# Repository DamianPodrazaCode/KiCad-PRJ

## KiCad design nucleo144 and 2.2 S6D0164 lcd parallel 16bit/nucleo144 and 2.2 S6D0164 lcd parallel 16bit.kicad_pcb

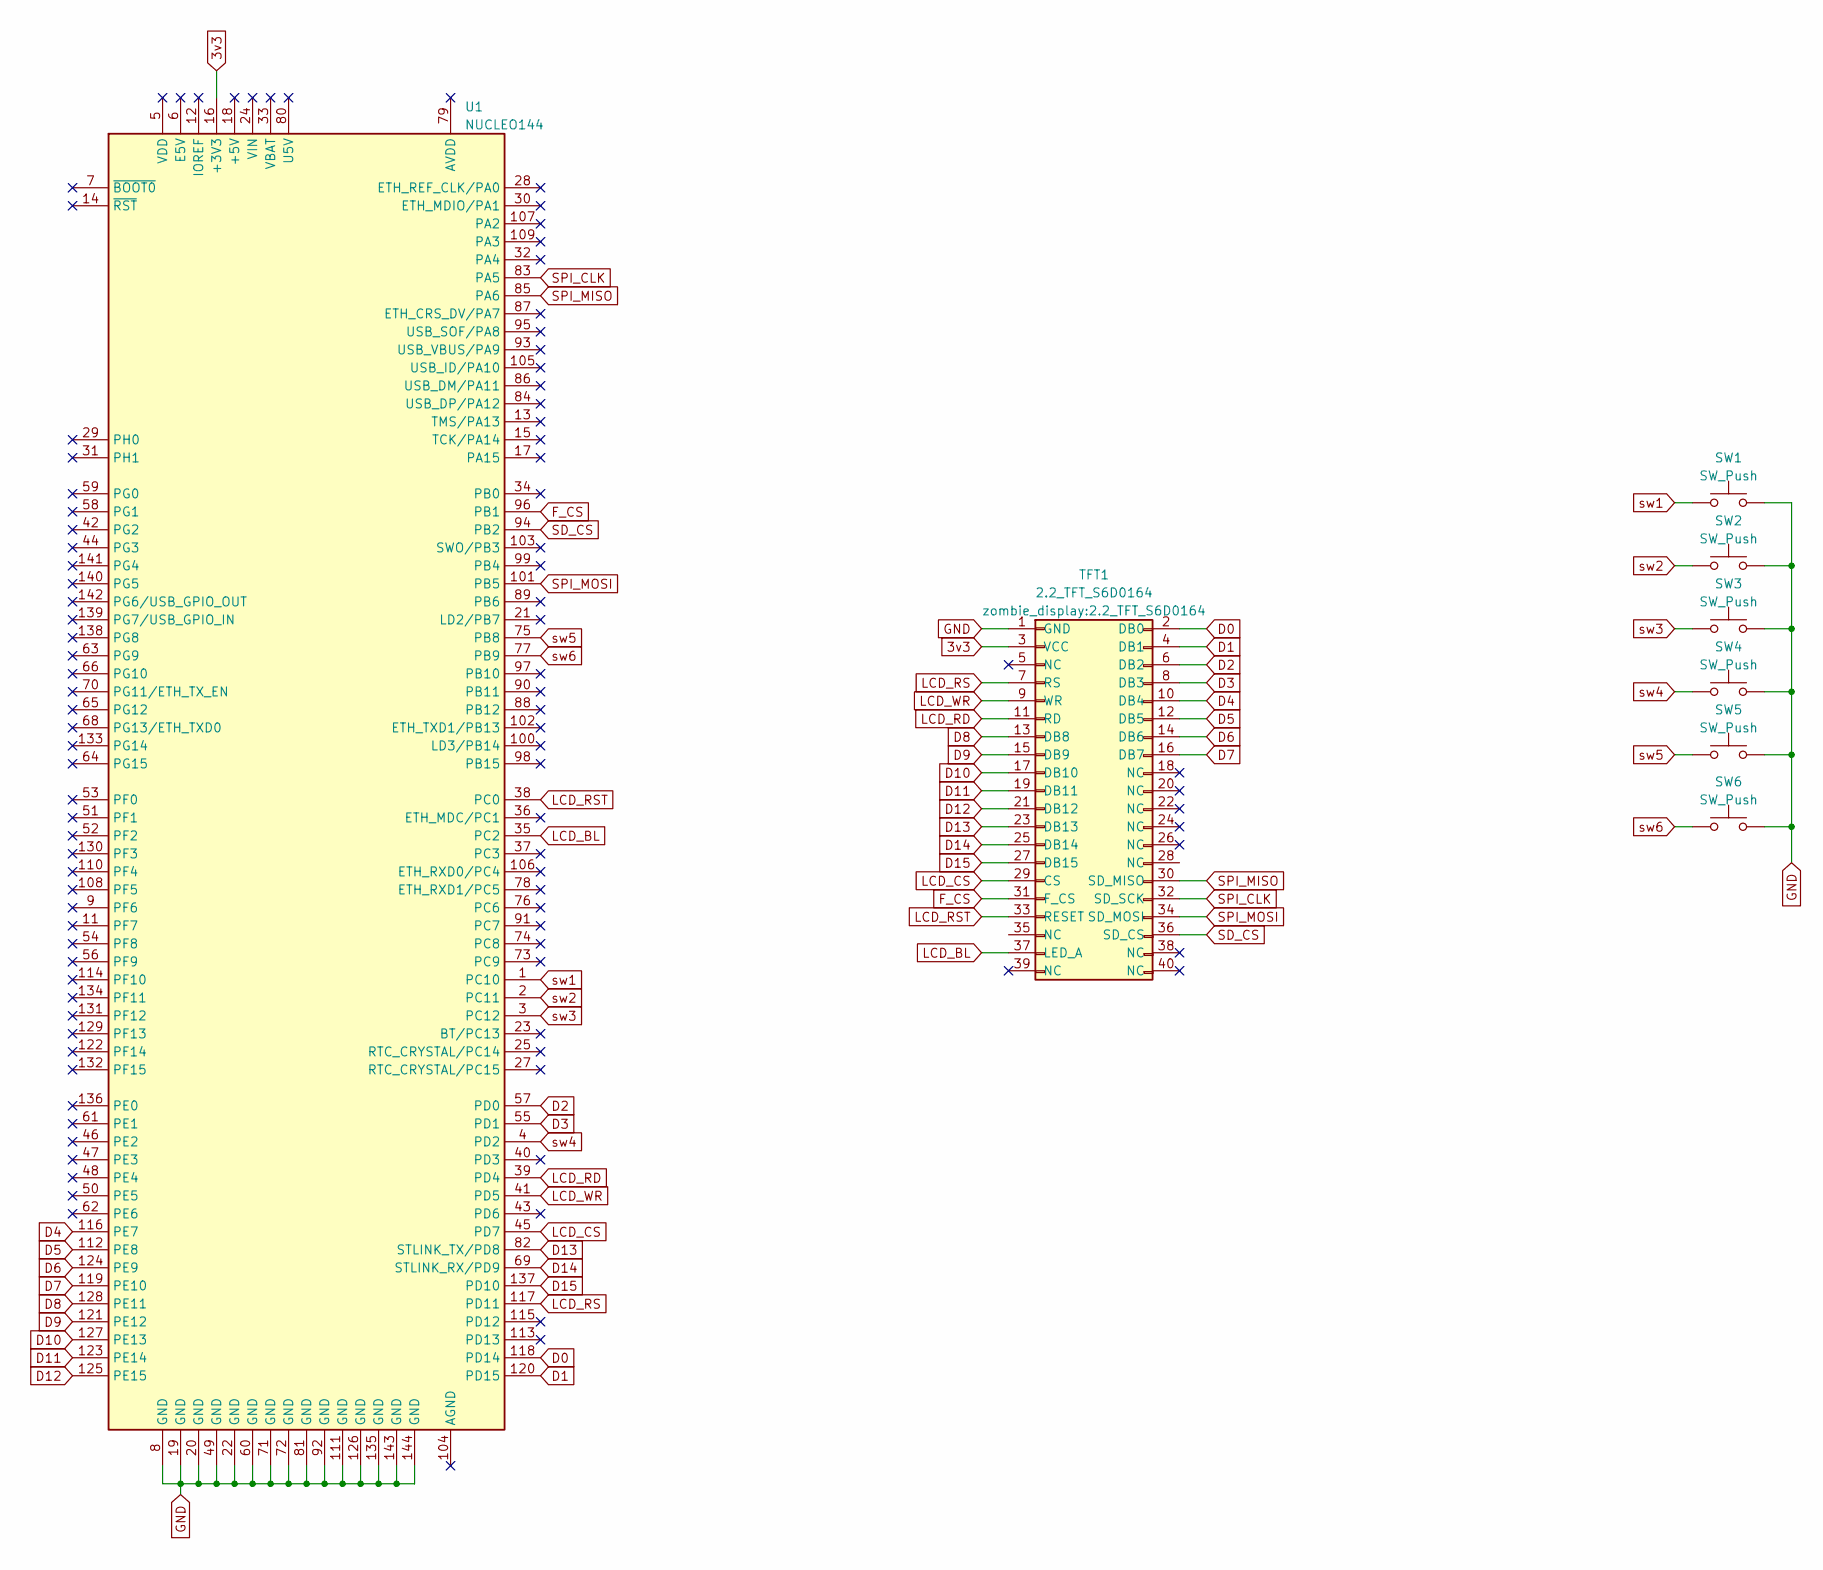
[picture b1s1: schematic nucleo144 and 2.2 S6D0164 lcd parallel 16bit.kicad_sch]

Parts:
SW1, SW2, SW3, SW4, SW5, SW6: SW_Push; SW_PUSH_6mm
TFT1: 2.2_TFT_S6D0164
U1: NUCLEO144; ST_Morpho_Connector_144_Short

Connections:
3v3: TFT1.3 (VCC), U1.16 (+3V3)
D0: TFT1.2 (DB0), U1.118 (PD14)
D1: TFT1.4 (DB1), U1.120 (PD15)
D2: TFT1.6 (DB2), U1.57 (PD0)
D3: TFT1.8 (DB3), U1.55 (PD1)
D4: TFT1.10 (DB4), U1.116 (PE7)
D5: TFT1.12 (DB5), U1.112 (PE8)
D6: TFT1.14 (DB6), U1.124 (PE9)
D7: TFT1.16 (DB7), U1.119 (PE10)
D8: TFT1.13 (DB8), U1.128 (PE11)
D9: TFT1.15 (DB9), U1.121 (PE12)
D10: TFT1.17 (DB10), U1.127 (PE13)
D11: TFT1.19 (DB11), U1.123 (PE14)
D12: TFT1.21 (DB12), U1.125 (PE15)
D13: TFT1.23 (DB13), U1.82 (STLINK_TX/PD8)
D14: TFT1.25 (DB14), U1.69 (STLINK_RX/PD9)
D15: TFT1.27 (DB15), U1.137 (PD10)
F_CS: TFT1.31 (F_CS), U1.96 (PB1)
GND: SW1.2, SW2.2, SW3.2, SW4.2, SW5.2, SW6.2, TFT1.1 (GND), U1.8 (GND), U1.19 (GND), U1.20 (GND), U1.22 (GND), U1.49 (GND), U1.60 (GND), U1.71 (GND), U1.72 (GND), U1.81 (GND), U1.92 (GND), U1.111 (GND), U1.126 (GND), U1.135 (GND), U1.143 (GND), U1.144 (GND)
LCD_BL: TFT1.37 (LED_A), U1.35 (PC2)
LCD_CS: TFT1.29 (CS), U1.45 (PD7)
LCD_RD: TFT1.11 (RD), U1.39 (PD4)
LCD_RS: TFT1.7 (RS), U1.117 (PD11)
LCD_RST: TFT1.33 (RESET), U1.38 (PC0)
LCD_WR: TFT1.9 (WR), U1.41 (PD5)
PEN: U1.37 (PC3)
SD_CS: TFT1.36 (SD_CS), U1.94 (PB2)
SPI_CLK: TFT1.32 (SD_SCK), U1.83 (PA5)
SPI_MISO: TFT1.30 (SD_MISO), U1.85 (PA6)
SPI_MOSI: TFT1.34 (SD_MOSI), U1.101 (PB5)
T_CS: U1.109 (PA3)
sw1: SW1.1, U1.1 (PC10)
sw2: SW2.1, U1.2 (PC11)
sw3: SW3.1, U1.3 (PC12)
sw4: SW4.1, U1.4 (PD2)
sw5: SW5.1, U1.75 (PB8)
sw6: SW6.1, U1.77 (PB9)

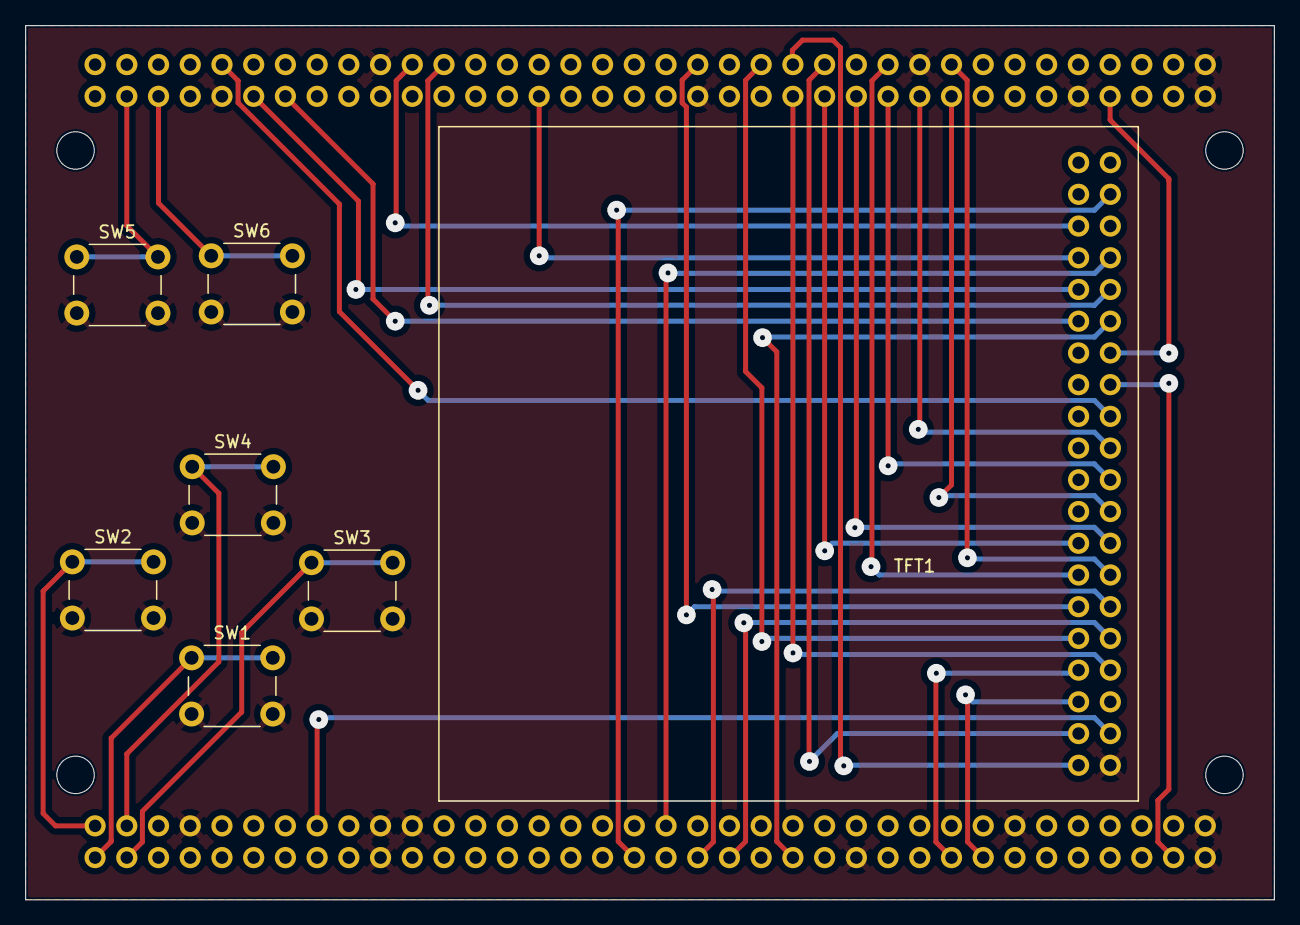
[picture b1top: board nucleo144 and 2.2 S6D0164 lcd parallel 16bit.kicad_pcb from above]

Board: 2 copper layers, 100.0 x 70.0 mm, 8 parts (0 on the bottom side), 35 nets.

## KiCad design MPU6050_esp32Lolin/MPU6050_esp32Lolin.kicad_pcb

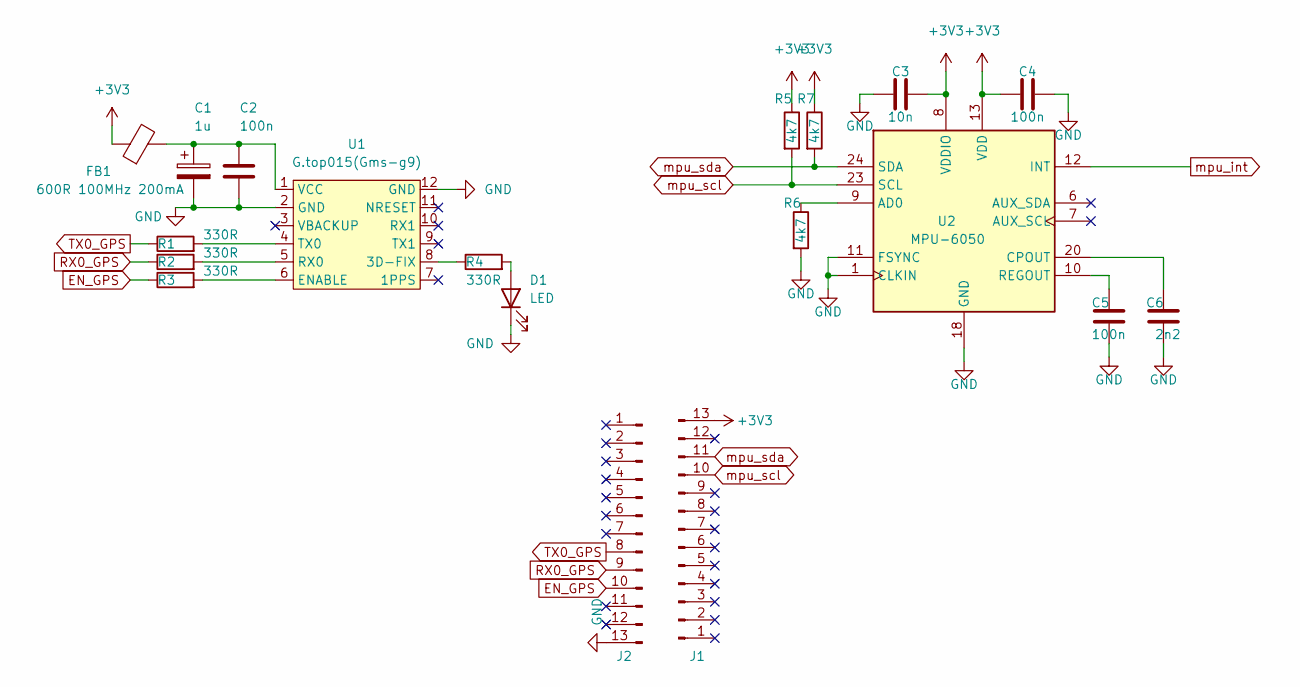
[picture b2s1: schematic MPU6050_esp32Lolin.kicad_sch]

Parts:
C1: 1u; CP_EIA-3528-21_Kemet-B_Pad1.50x2.35mm_HandSolder
C2: 100n; C_1206_3216Metric_Pad1.33x1.80mm_HandSolder
C3: 10n; C_0805_2012Metric_Pad1.18x1.45mm_HandSolder
C4, C5: 100n; C_0805_2012Metric_Pad1.18x1.45mm_HandSolder
C6: 2n2; C_0805_2012Metric_Pad1.18x1.45mm_HandSolder
D1: LED; LED_1206_3216Metric_Pad1.42x1.75mm_HandSolder
FB1: 600R 100MHz 200mA; L_1206_3216Metric_Pad1.22x1.90mm_HandSolder
J1, J2: Conn_01x13_Male; PinHeader_1x13_P2.54mm_Vertical
R1, R2, R3, R4: 330R; R_0805_2012Metric_Pad1.20x1.40mm_HandSolder
R5, R6, R7: 4k7; R_0805_2012Metric_Pad1.20x1.40mm_HandSolder
U1: G.top015(Gms-g9); G.top015(Gsm-g9)
U2: MPU-6050; InvenSense_QFN-24_4x4mm_P0.5mm

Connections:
+3V3: C3.1, C4.1, FB1.1, J1.13, R5.1, R7.1, U2.8 (VDDIO), U2.13 (VDD)
EN_GPS: J2.10, R3.1
GND: C1.2, C2.2, C3.2, C4.2, C5.2, C6.2, D1.1 (K), J2.13, R6.2, U1.2 (GND), U1.12 (GND), U2.1 (CLKIN), U2.11 (FSYNC), U2.18 (GND)
unnamed: C1.1, C2.1, FB1.2, U1.1 (VCC)
unnamed: C5.1, U2.10 (REGOUT)
unnamed: C6.1, U2.20 (CPOUT)
unnamed: D1.2 (A), R4.2
unnamed: R1.2, U1.4 (TX0)
unnamed: R2.2, U1.5 (RX0)
unnamed: R3.2, U1.6 (ENABLE)
unnamed: R4.1, U1.8 (3D-FIX)
unnamed: R6.1, U2.9 (AD0)
RX0_GPS: J2.9, R2.1
TX0_GPS: J2.8, R1.1
mpu_int: U2.12 (INT)
mpu_scl: J1.10, R5.2, U2.23 (SCL)
mpu_sda: J1.11, R7.2, U2.24 (SDA)

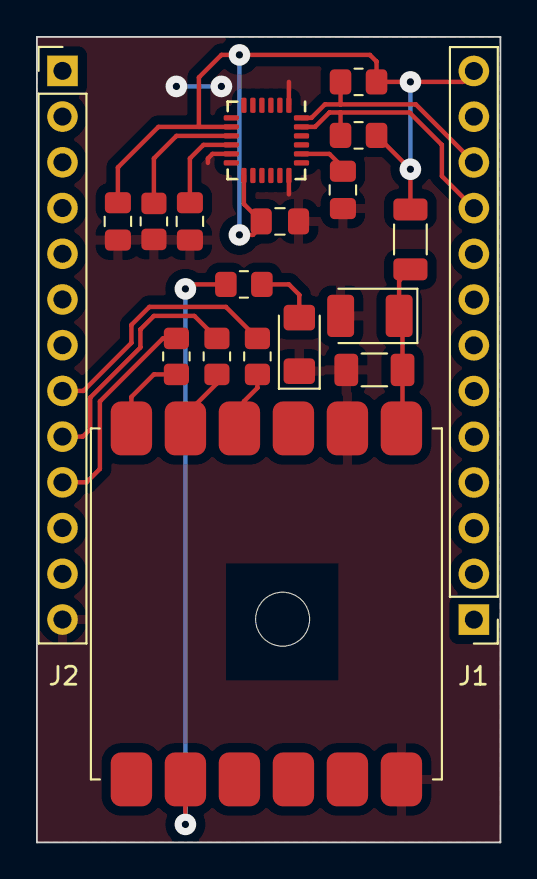
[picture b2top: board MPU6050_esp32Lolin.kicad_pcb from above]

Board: 2 copper layers, 25.8 x 44.8 mm, 19 parts (0 on the bottom side), 16 nets.

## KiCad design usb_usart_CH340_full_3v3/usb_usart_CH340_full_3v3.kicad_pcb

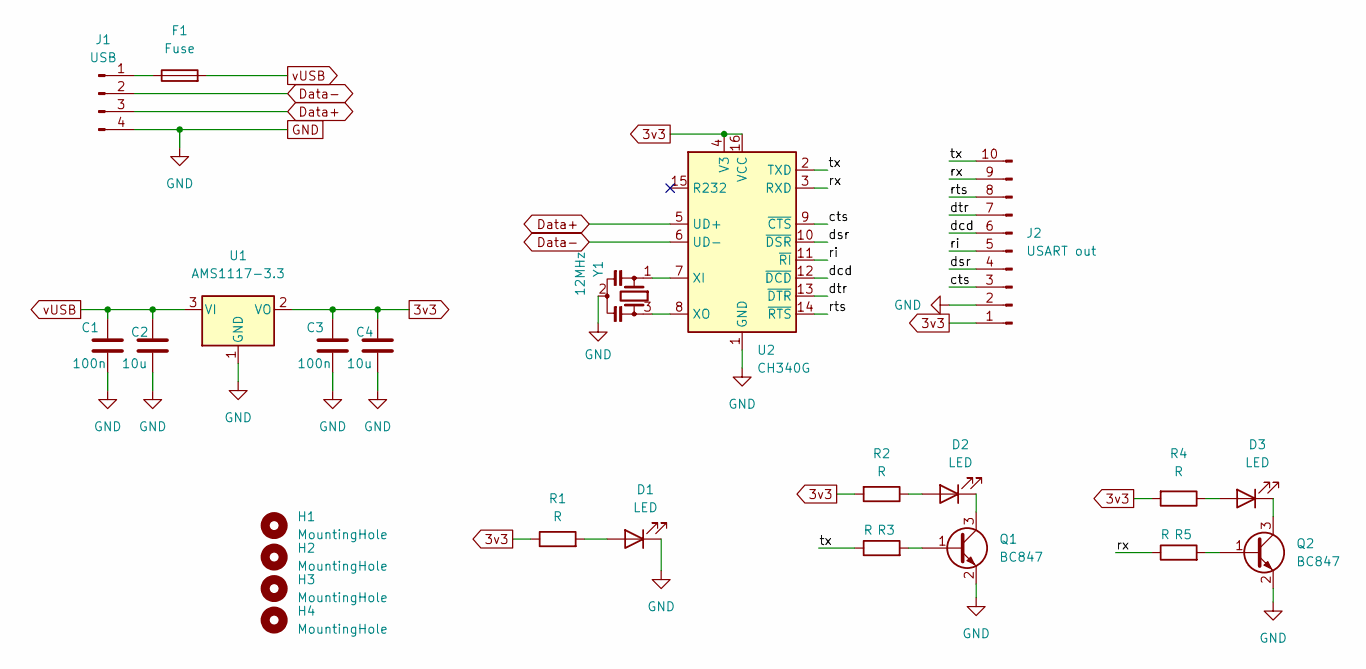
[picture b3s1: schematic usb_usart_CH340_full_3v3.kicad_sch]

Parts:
C1, C3: 100n; C_1206_3216Metric_Pad1.33x1.80mm_HandSolder
C2, C4: 10u; C_1206_3216Metric_Pad1.33x1.80mm_HandSolder
D1, D2, D3: LED; LED_0805_2012Metric_Pad1.15x1.40mm_HandSolder
F1: Fuse; Fuse_1812_4532Metric_Pad1.30x3.40mm_HandSolder
H1, H2, H3, H4: MountingHole; MountingHole_3mm_Pad_TopOnly
J1: USB; PinHeader_1x04_P2.54mm_Horizontal
J2: USART out; PinSocket_1x10_P2.54mm_Horizontal
Q1, Q2: BC847; SOT-23
R1, R2, R3, R4, R5: R; R_1206_3216Metric_Pad1.30x1.75mm_HandSolder
U1: AMS1117-3.3; SOT-223-3_TabPin2
U2: CH340G; SOP-16_3.9x9.9mm_P1.27mm
Y1: 12MHz; Resonator_SMD_Murata_CSTxExxV-3Pin_3.0x1.1mm_HandSoldering

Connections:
3v3: C3.1, C4.1, J2.1, R1.1, R2.2, R4.2, U1.2 (VO), U2.4 (V3), U2.16 (VCC)
/cts: J2.3, U2.9 (~CTS)
/dcd: J2.6, U2.12 (~DCD)
/dsr: J2.4, U2.10 (~DSR)
/dtr: J2.7, U2.13 (~DTR)
/ri: J2.5, U2.11 (~RI)
/rts: J2.8, U2.14 (~RTS)
/rx: J2.9, R5.1, U2.3 (RXD)
/tx: J2.10, R3.1, U2.2 (TXD)
Data+: J1.3, U2.5 (UD+)
Data-: J1.2, U2.6 (UD-)
GND: C1.2, C2.2, C3.2, C4.2, D1.1 (K), J1.4, J2.2, Q1.2 (E), Q2.2 (E), U1.1 (GND), U2.1 (GND), Y1.2
unnamed: D1.2 (A), R1.2
unnamed: D2.1 (K), Q1.3 (C)
unnamed: D2.2 (A), R2.1
unnamed: D3.1 (K), Q2.3 (C)
unnamed: D3.2 (A), R4.1
unnamed: F1.1, J1.1
unnamed: Q1.1 (B), R3.2
unnamed: Q2.1 (B), R5.2
unnamed: U2.7 (XI), Y1.1
unnamed: U2.8 (XO), Y1.3
vUSB: C1.1, C2.1, F1.2, U1.3 (VI)

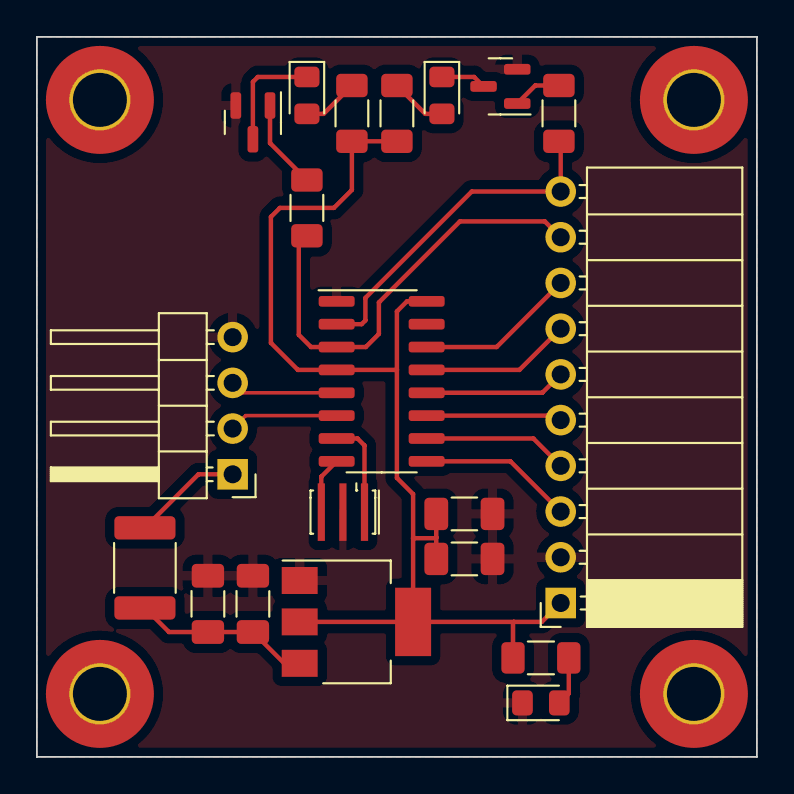
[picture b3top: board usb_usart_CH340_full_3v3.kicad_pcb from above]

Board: 2 copper layers, 40.0 x 40.0 mm, 24 parts (0 on the bottom side), 23 nets.

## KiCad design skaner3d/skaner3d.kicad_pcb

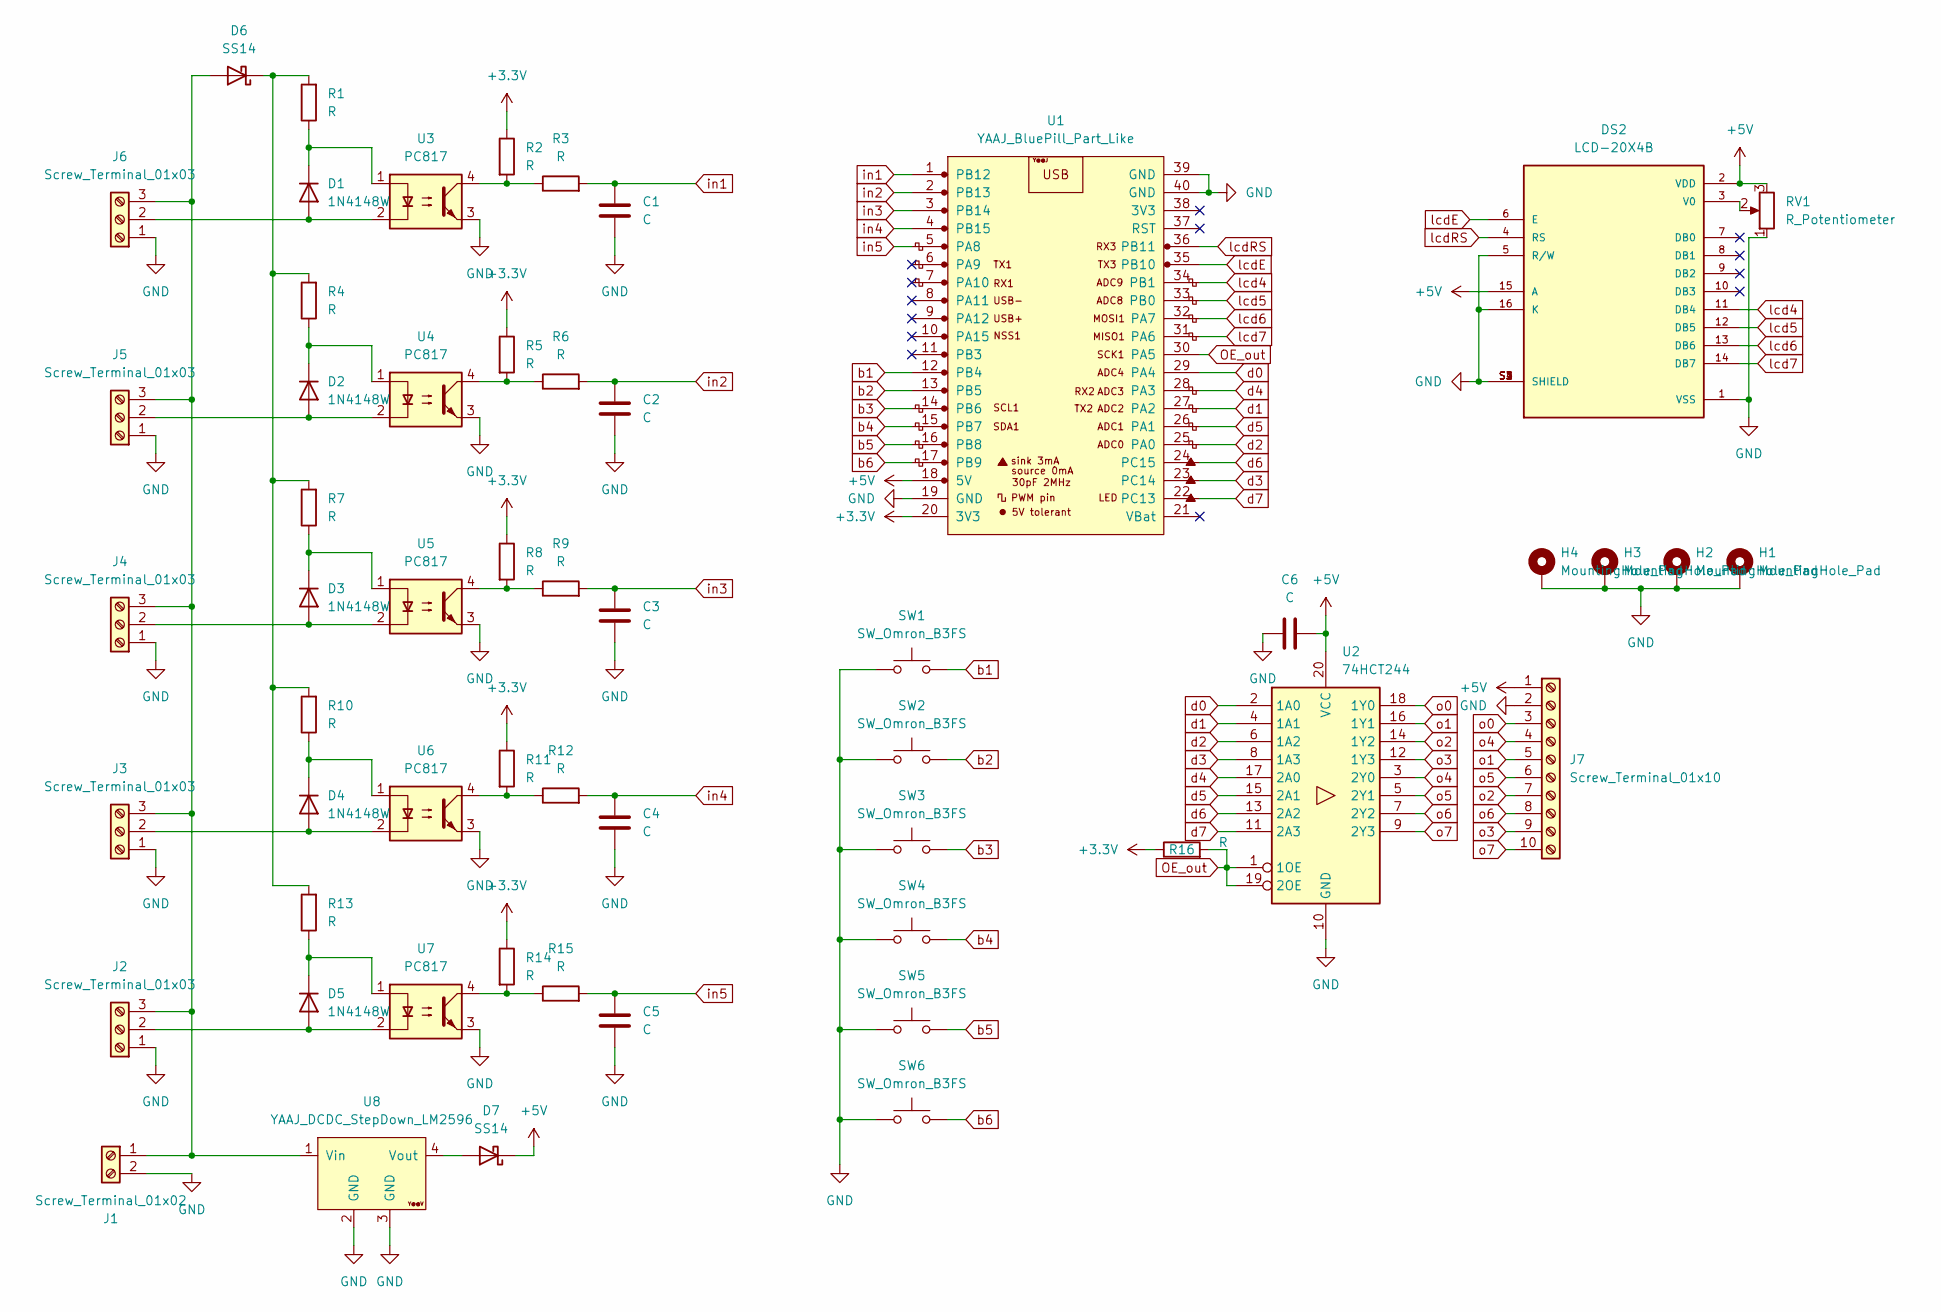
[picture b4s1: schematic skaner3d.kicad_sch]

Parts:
C1, C2, C3, C4, C5, C6: C; C_1206_3216Metric_Pad1.33x1.80mm_HandSolder
D1, D2, D3, D4, D5: 1N4148W; D_SOD-123
D6, D7: SS14; D_SMA
DS2: LCD-20X4B; LCD_LCD-20X4B
H1, H2, H3, H4: MountingHole_Pad; MountingHole_3.2mm_M3_ISO14580_Pad
J1: Screw_Terminal_01x02; PhoenixContact_MSTBVA_2,5_2-G-5,08_1x02_P5.08mm_Vertical
J2, J3, J4, J5, J6: Screw_Terminal_01x03; PhoenixContact_MSTBVA_2,5_3-G-5,08_1x03_P5.08mm_Vertical
J7: Screw_Terminal_01x10; PhoenixContact_MSTBVA_2,5_10-G-5,08_1x10_P5.08mm_Vertical
R1, R2, R3, R4, R5, R6, R7, R8, R9, R10, R11, R12, R13, R14, R15, R16: R; R_1206_3216Metric_Pad1.30x1.75mm_HandSolder
RV1: R_Potentiometer; Potentiometer_Vishay_T93YA_Vertical
SW1, SW2, SW3, SW4, SW5, SW6: SW_Omron_B3FS; SW_PUSH_6mm_H5mm
U1: YAAJ_BluePill_Part_Like; YAAJ_BluePill_2
U2: 74HCT244; CERDIP-20_W7.62mm_SideBrazed
U3, U4, U5, U6, U7: PC817; DIP-4_W7.62mm
U8: YAAJ_DCDC_StepDown_LM2596

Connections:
+3.3V: R2.1, R5.1, R8.1, R11.1, R14.1, R16.1, U1.20 (3V3)
+5V: C6.2, D7.1 (K), DS2.2 (VDD), DS2.15 (A), J7.1, RV1.3, U1.18 (5V), U2.20 (VCC)
GND: C1.2, C2.2, C3.2, C4.2, C5.2, C6.1, DS2.1 (VSS), DS2.5 (R/W), DS2.16 (K), DS2.S1 (SHIELD), DS2.S2 (SHIELD), DS2.S3 (SHIELD), DS2.S4 (SHIELD), H1.1, H2.1, H3.1, H4.1, J1.2, J2.1, J3.1, J4.1, J5.1, J6.1, J7.2, RV1.1, SW1.1, SW2.1, SW3.1, SW4.1, SW5.1, SW6.1, U1.19 (GND), U1.39 (GND), U1.40 (GND), U2.10 (GND), U3.3, U4.3, U5.3, U6.3, U7.3, U8.2 (GND), U8.3 (GND)
unnamed: D1.2 (A), J6.2, U3.2
unnamed: D1.1 (K), R1.1, U3.1
unnamed: D2.2 (A), J5.2, U4.2
unnamed: D2.1 (K), R4.1, U4.1
unnamed: D3.2 (A), J4.2, U5.2
unnamed: D3.1 (K), R7.1, U5.1
unnamed: D4.2 (A), J3.2, U6.2
unnamed: D4.1 (K), R10.1, U6.1
unnamed: D5.2 (A), J2.2, U7.2
unnamed: D5.1 (K), R13.1, U7.1
unnamed: D6.2 (A), J1.1, J2.3, J3.3, J4.3, J5.3, J6.3, U8.1 (Vin)
unnamed: D6.1 (K), R1.2, R4.2, R7.2, R10.2, R13.2
unnamed: D7.2 (A), U8.4 (Vout)
unnamed: DS2.3 (V0), RV1.2
unnamed: R2.2, R3.1, U3.4
unnamed: R5.2, R6.1, U4.4
unnamed: R8.2, R9.1, U5.4
unnamed: R11.2, R12.1, U6.4
unnamed: R14.2, R15.1, U7.4
OE_out: R16.2, U1.30 (PA5), U2.1 (1OE), U2.19 (2OE)
b1: SW1.2, U1.12 (PB4)
b2: SW2.2, U1.13 (PB5)
b3: SW3.2, U1.14 (PB6)
b4: SW4.2, U1.15 (PB7)
b5: SW5.2, U1.16 (PB8)
b6: SW6.2, U1.17 (PB9)
d0: U1.29 (PA4), U2.2 (1A0)
d1: U1.27 (PA2), U2.4 (1A1)
d2: U1.25 (PA0), U2.6 (1A2)
d3: U1.23 (PC14), U2.8 (1A3)
d4: U1.28 (PA3), U2.17 (2A0)
d5: U1.26 (PA1), U2.15 (2A1)
d6: U1.24 (PC15), U2.13 (2A2)
d7: U1.22 (PC13), U2.11 (2A3)
in1: C1.1, R3.2, U1.1 (PB12)
in2: C2.1, R6.2, U1.2 (PB13)
in3: C3.1, R9.2, U1.3 (PB14)
in4: C4.1, R12.2, U1.4 (PB15)
in5: C5.1, R15.2, U1.5 (PA8)
lcd4: DS2.11 (DB4), U1.34 (PB1)
lcd5: DS2.12 (DB5), U1.33 (PB0)
lcd6: DS2.13 (DB6), U1.32 (PA7)
lcd7: DS2.14 (DB7), U1.31 (PA6)
lcdE: DS2.6 (E), U1.35 (PB10)
lcdRS: DS2.4 (RS), U1.36 (PB11)
o0: J7.3, U2.18 (1Y0)
o1: J7.5, U2.16 (1Y1)
o2: J7.7, U2.14 (1Y2)
o3: J7.9, U2.12 (1Y3)
o4: J7.4, U2.3 (2Y0)
o5: J7.6, U2.5 (2Y1)
o6: J7.8, U2.7 (2Y2)
o7: J7.10, U2.9 (2Y3)

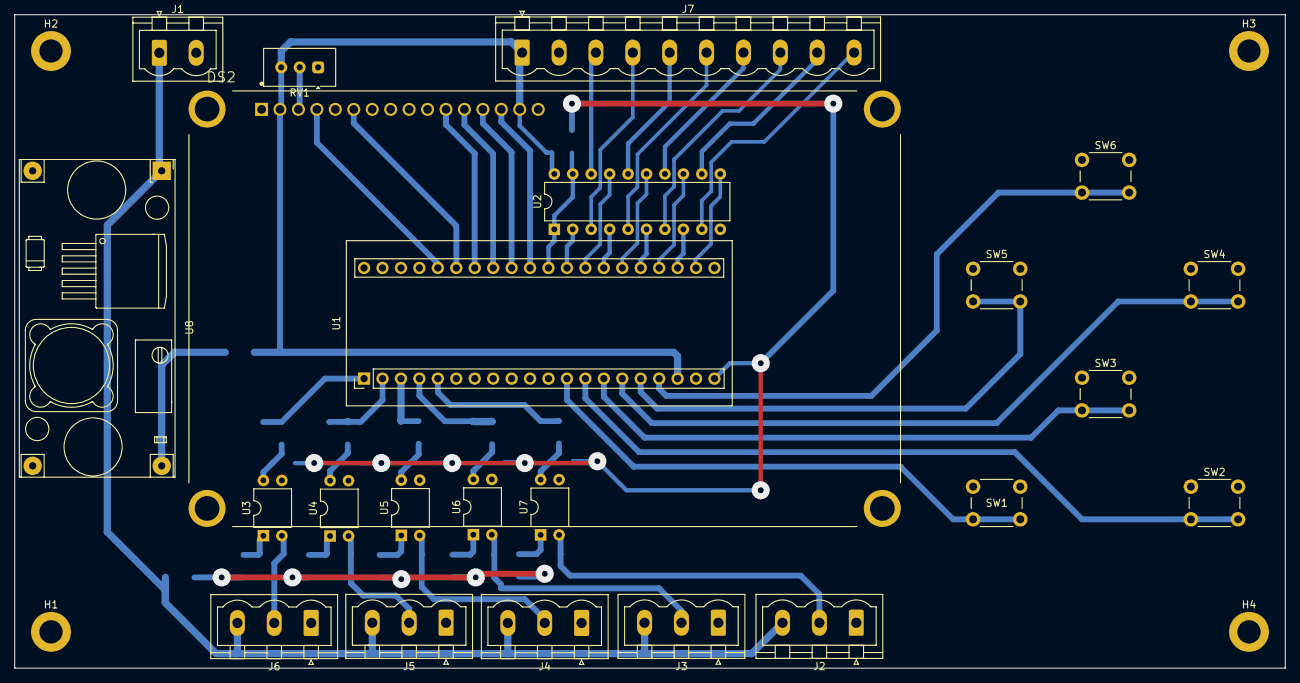
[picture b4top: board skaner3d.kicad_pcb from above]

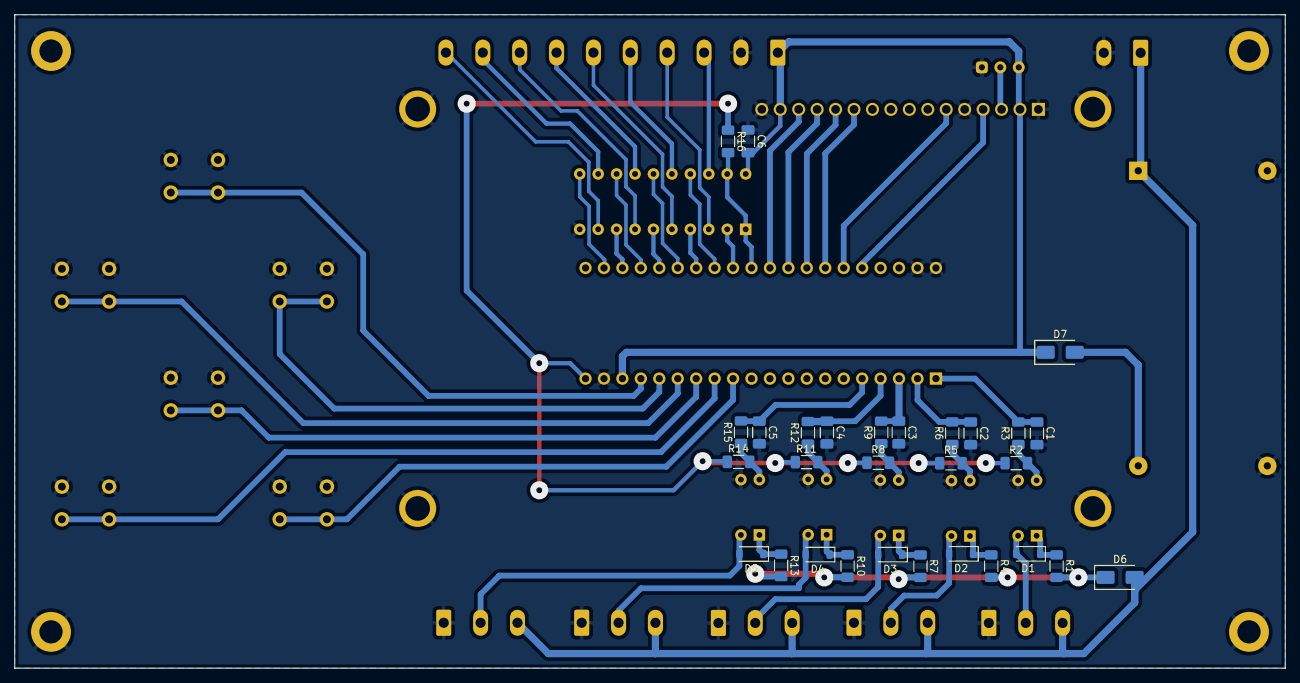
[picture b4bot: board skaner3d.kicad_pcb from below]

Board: 2 copper layers, 175.0 x 90.0 mm, 56 parts (29 on the bottom side), 56 nets.

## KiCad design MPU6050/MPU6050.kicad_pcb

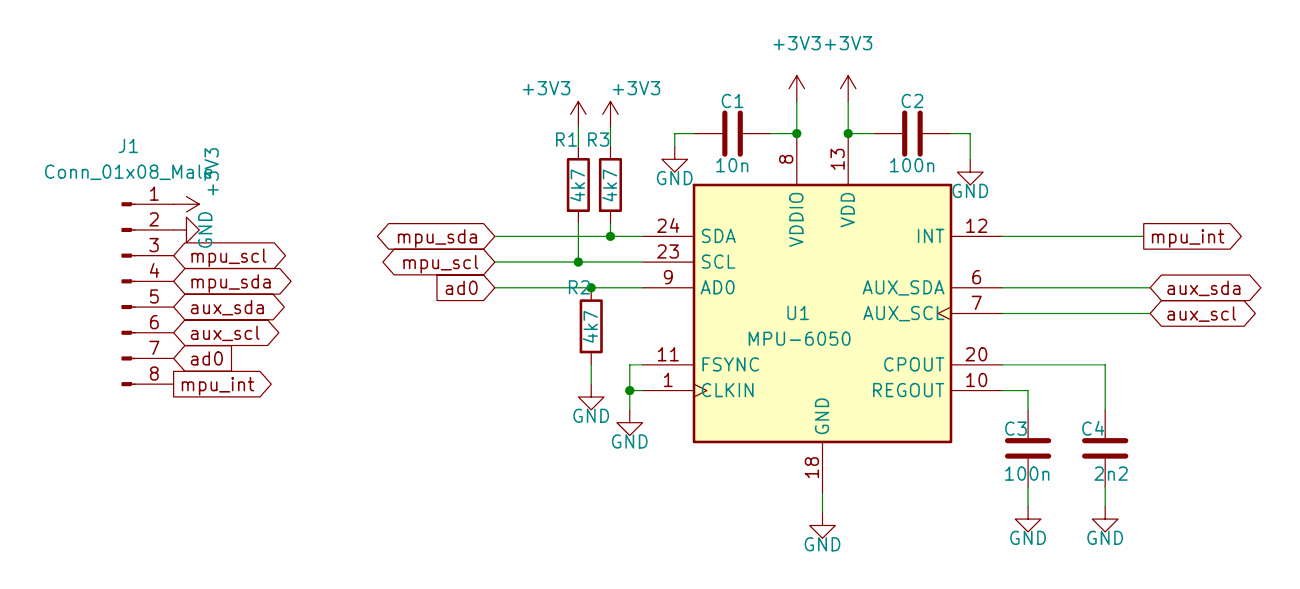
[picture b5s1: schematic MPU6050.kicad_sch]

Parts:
C1: 10n; C_0805_2012Metric_Pad1.18x1.45mm_HandSolder
C2: 100n; C_0805_2012Metric_Pad1.18x1.45mm_HandSolder
C3: 100n; C_1206_3216Metric_Pad1.33x1.80mm_HandSolder
C4: 2n2; C_1206_3216Metric_Pad1.33x1.80mm_HandSolder
J1: Conn_01x08_Male; PinHeader_1x08_P2.54mm_Vertical
R1, R2: 4k7; R_0805_2012Metric_Pad1.20x1.40mm_HandSolder
R3: 4k7; R_1206_3216Metric_Pad1.30x1.75mm_HandSolder
U1: MPU-6050; InvenSense_QFN-24_4x4mm_P0.5mm

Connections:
+3V3: C1.1, C2.1, J1.1, R1.1, R3.1, U1.8 (VDDIO), U1.13 (VDD)
GND: C1.2, C2.2, C3.2, C4.2, J1.2, R2.2, U1.1 (CLKIN), U1.11 (FSYNC), U1.18 (GND)
unnamed: C3.1, U1.10 (REGOUT)
unnamed: C4.1, U1.20 (CPOUT)
ad0: J1.7, R2.1, U1.9 (AD0)
aux_scl: J1.6, U1.7 (AUX_SCL)
aux_sda: J1.5, U1.6 (AUX_SDA)
mpu_int: J1.8, U1.12 (INT)
mpu_scl: J1.3, R1.2, U1.23 (SCL)
mpu_sda: J1.4, R3.2, U1.24 (SDA)

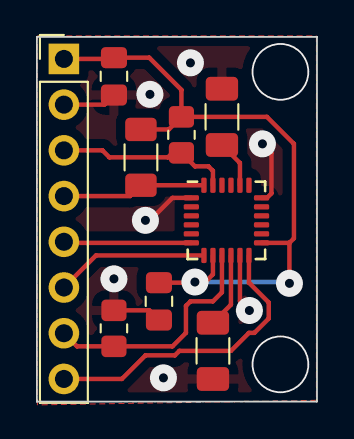
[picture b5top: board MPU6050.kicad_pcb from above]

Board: 2 copper layers, 15.6 x 20.3 mm, 9 parts (0 on the bottom side), 10 nets.

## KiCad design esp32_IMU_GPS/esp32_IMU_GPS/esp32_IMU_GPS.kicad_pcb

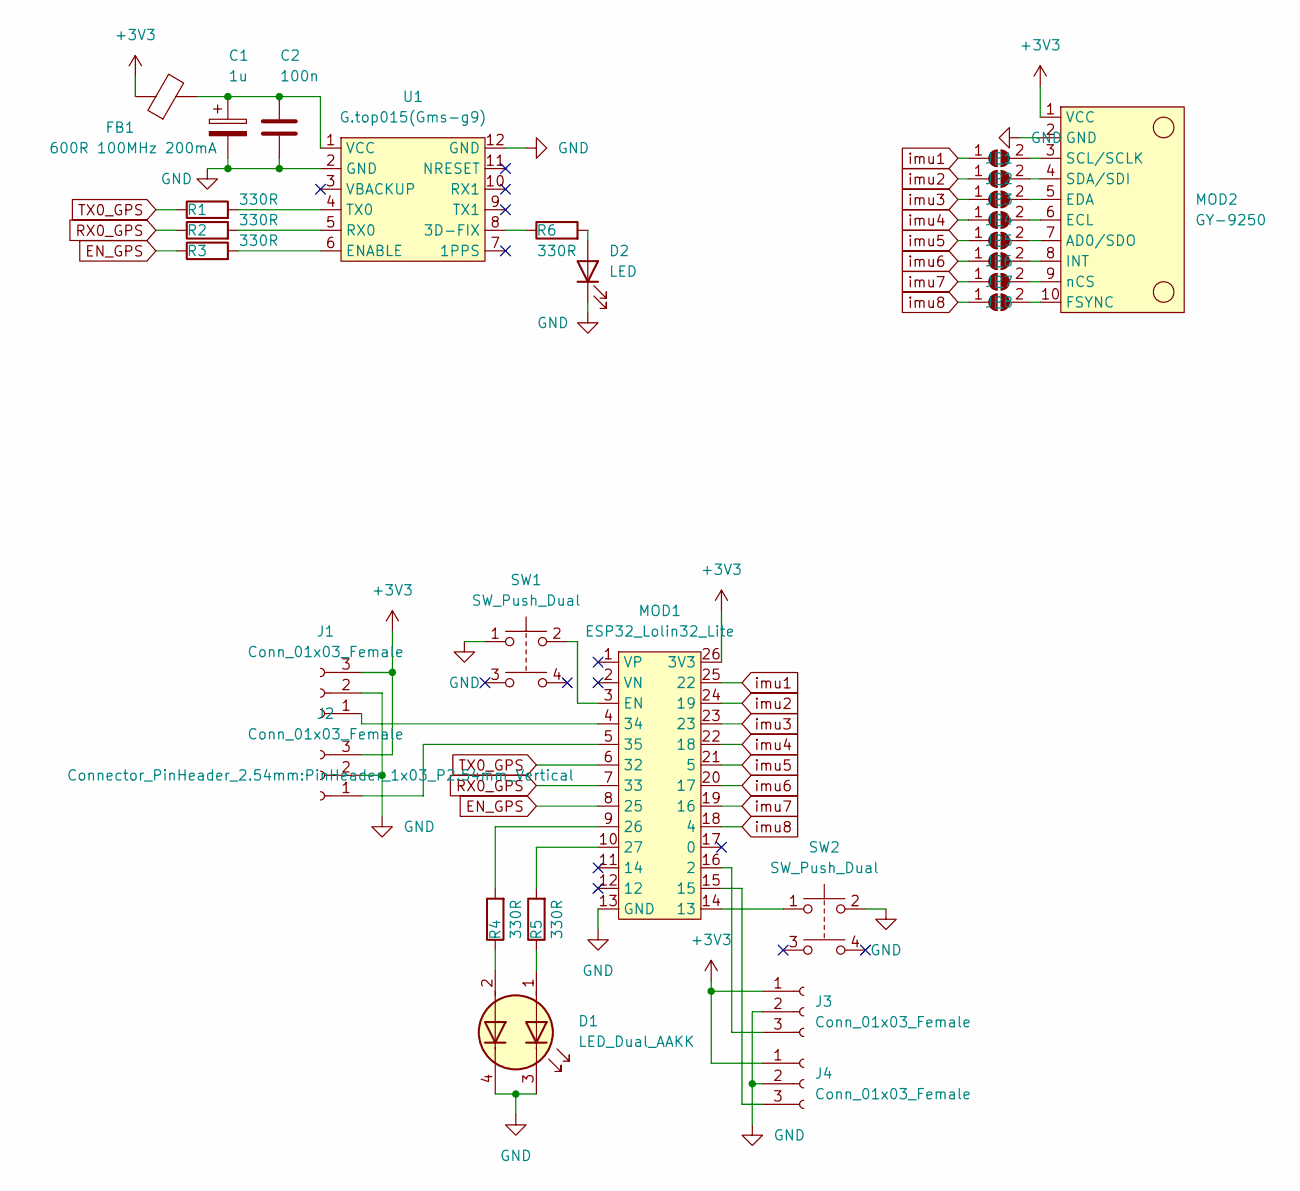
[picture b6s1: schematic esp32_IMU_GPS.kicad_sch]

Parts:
C1: 1u; CP_EIA-3528-21_Kemet-B_Pad1.50x2.35mm_HandSolder
C2: 100n; C_1206_3216Metric_Pad1.33x1.80mm_HandSolder
D1: LED_Dual_AAKK; LED_Avago_PLCC4_3.2x2.8mm_CW
D2: LED; LED_1206_3216Metric_Pad1.42x1.75mm_HandSolder
FB1: 600R 100MHz 200mA; L_6.3x6.3_H3
J1, J2, J3, J4: Conn_01x03_Female; PinHeader_1x03_P2.54mm_Vertical
JP1, JP2, JP3, JP4, JP5, JP6, JP7, JP8: _; SolderJumper-2_P1.3mm_Open_TrianglePad1.0x1.5mm
MOD1: ESP32_Lolin32_Lite
MOD2: GY-9250; IMU_10pin
R1, R2, R3, R4, R5, R6: 330R; R_0805_2012Metric_Pad1.20x1.40mm_HandSolder
SW1, SW2: SW_Push_Dual; SW_PUSH_6mm
U1: G.top015(Gms-g9); G.top015(Gsm-g9)

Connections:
+3V3: FB1.1, J1.3, J2.3, J3.1, J4.1, MOD1.26 (3V3), MOD2.1 (VCC)
EN_GPS: MOD1.8 (25), R3.1
GND: C1.2, C2.2, D1.3 (K1), D1.4 (K2), D2.1 (K), J1.2, J2.2, J3.2, J4.2, MOD1.13 (GND), MOD2.2 (GND), SW1.1, SW2.2, U1.2 (GND), U1.12 (GND)
unnamed: C1.1, C2.1, FB1.2, U1.1 (VCC)
unnamed: D1.1 (A1), R5.1
unnamed: D1.2 (A2), R4.1
unnamed: D2.2 (A), R6.2
unnamed: J1.1, MOD1.4 (34)
unnamed: J2.1, MOD1.5 (35)
unnamed: J3.3, MOD1.16 (2)
unnamed: J4.3, MOD1.15
unnamed: JP1.2 (B), MOD2.3 (SCL/SCLK)
unnamed: JP2.2 (B), MOD2.4 (SDA/SDI)
unnamed: JP3.2 (B), MOD2.5 (EDA)
unnamed: JP4.2 (B), MOD2.6 (ECL)
unnamed: JP5.2 (B), MOD2.7 (AD0/SDO)
unnamed: JP6.2 (B), MOD2.8 (INT)
unnamed: JP7.2 (B), MOD2.9 (nCS)
unnamed: JP8.2 (B), MOD2.10 (FSYNC)
unnamed: MOD1.9 (26), R4.2
unnamed: MOD1.10 (27), R5.2
unnamed: MOD1.14 (13), SW2.1
unnamed: R1.2, U1.4 (TX0)
unnamed: R2.2, U1.5 (RX0)
unnamed: R3.2, U1.6 (ENABLE)
unnamed: R6.1, U1.8 (3D-FIX)
unnamed: MOD1.3 (EN), SW1.2
RX0_GPS: MOD1.7 (33), R2.1
TX0_GPS: MOD1.6 (32), R1.1
imu1: JP1.1 (A), MOD1.25 (22)
imu2: JP2.1 (A), MOD1.24 (19)
imu3: JP3.1 (A), MOD1.23
imu4: JP4.1 (A), MOD1.22 (18)
imu5: JP5.1 (A), MOD1.21 (5)
imu6: JP6.1 (A), MOD1.20 (17)
imu7: JP7.1 (A), MOD1.19 (16)
imu8: JP8.1 (A), MOD1.18 (4)

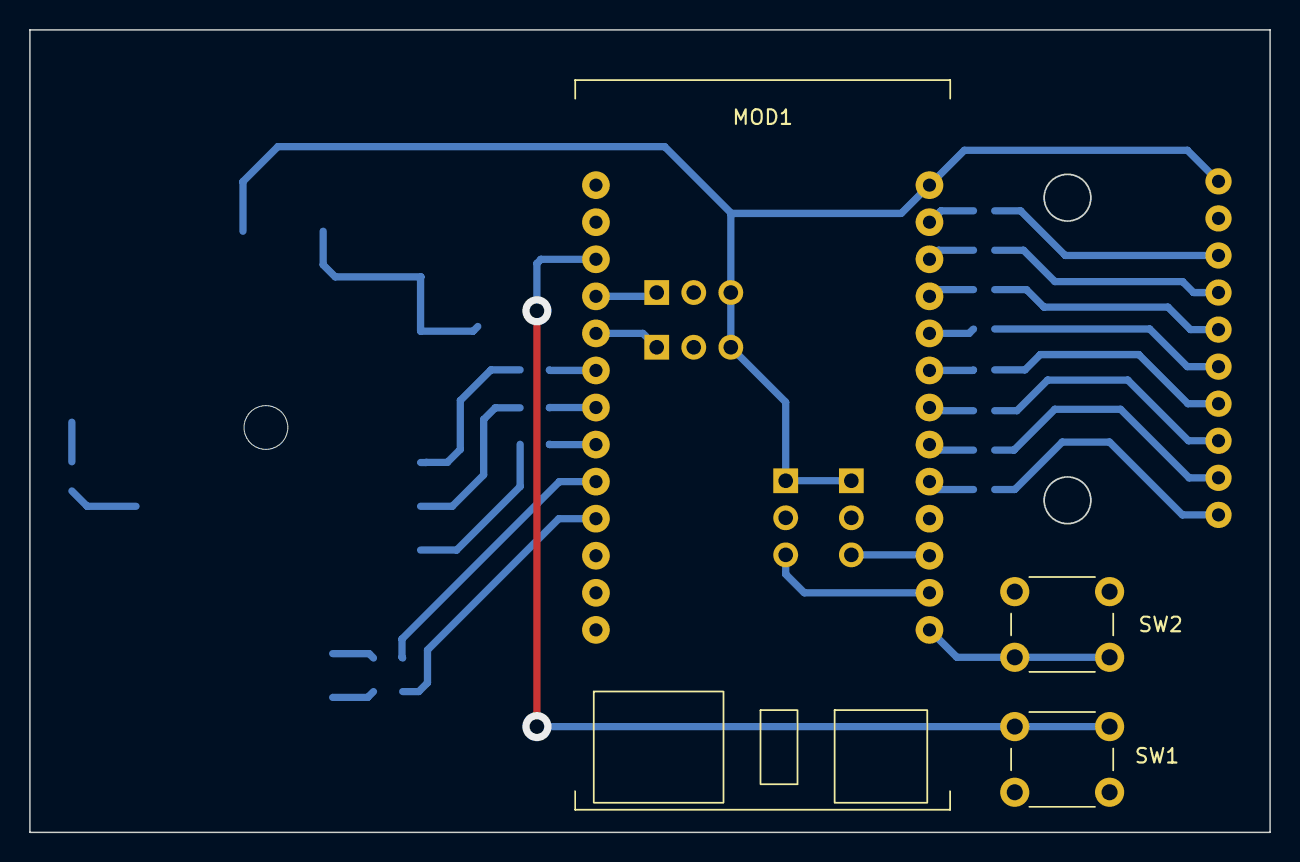
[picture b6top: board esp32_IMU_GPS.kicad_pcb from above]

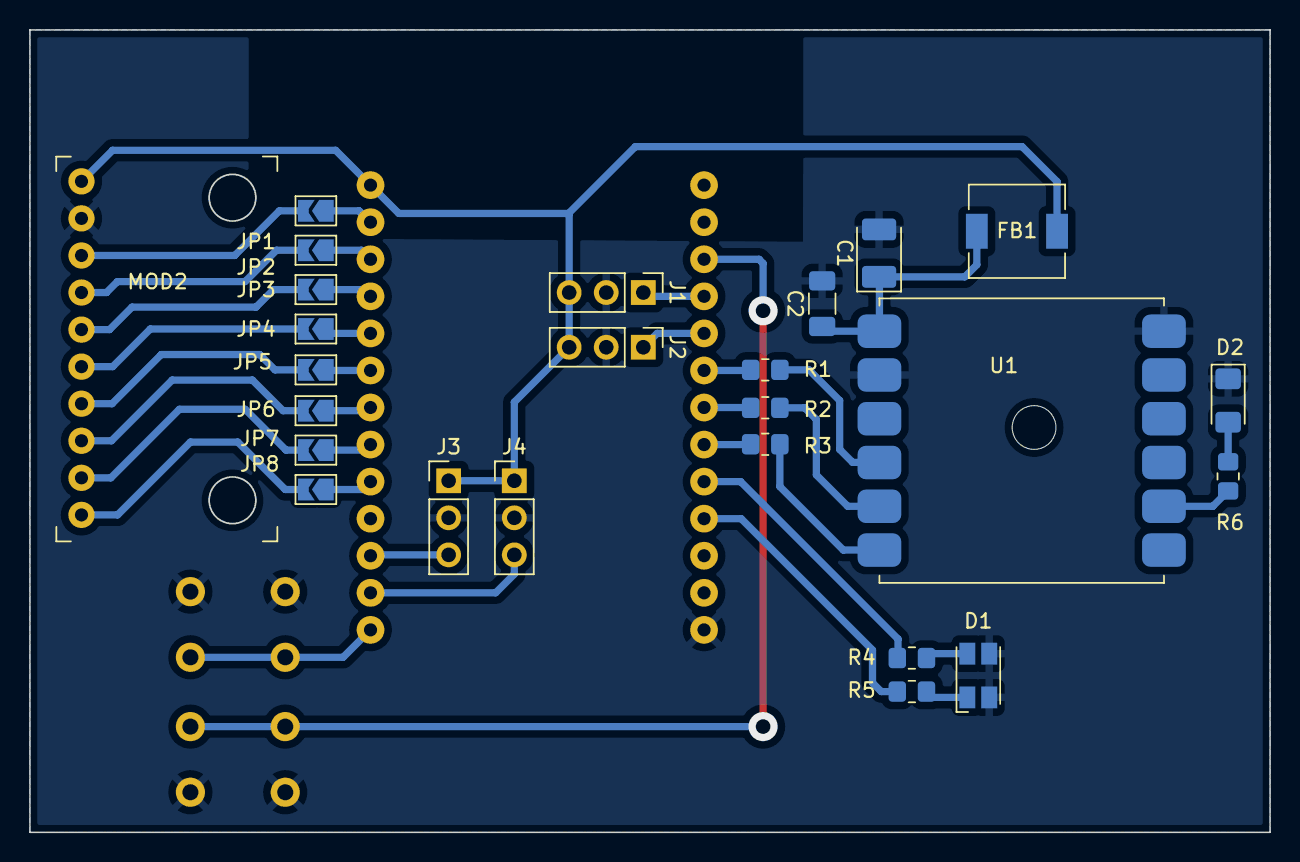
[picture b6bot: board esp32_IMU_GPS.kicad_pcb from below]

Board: 2 copper layers, 85.0 x 55.0 mm, 28 parts (25 on the bottom side), 37 nets.
